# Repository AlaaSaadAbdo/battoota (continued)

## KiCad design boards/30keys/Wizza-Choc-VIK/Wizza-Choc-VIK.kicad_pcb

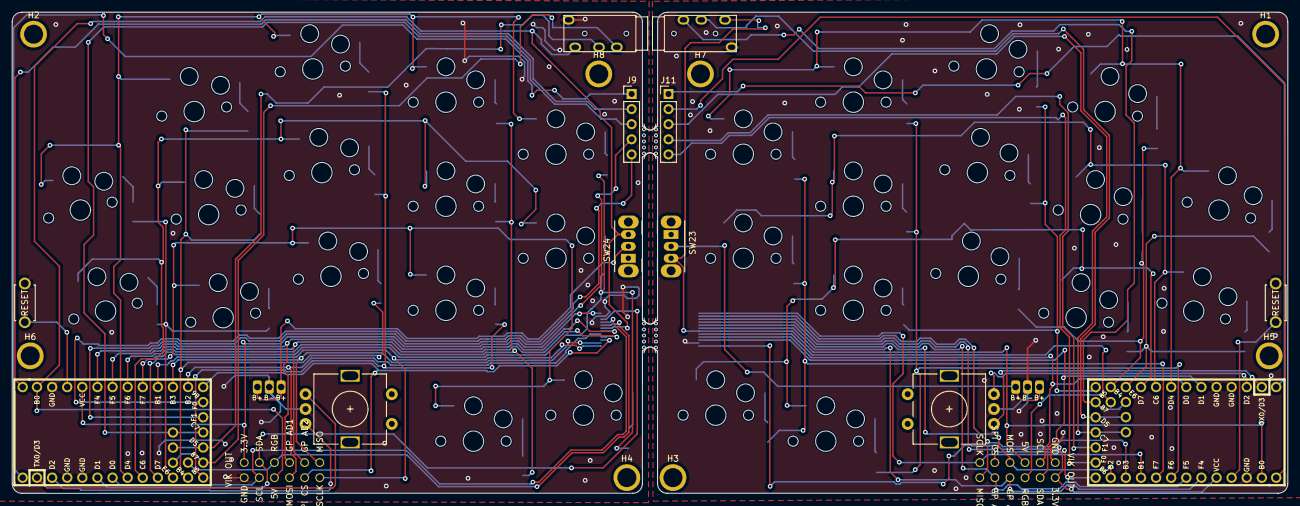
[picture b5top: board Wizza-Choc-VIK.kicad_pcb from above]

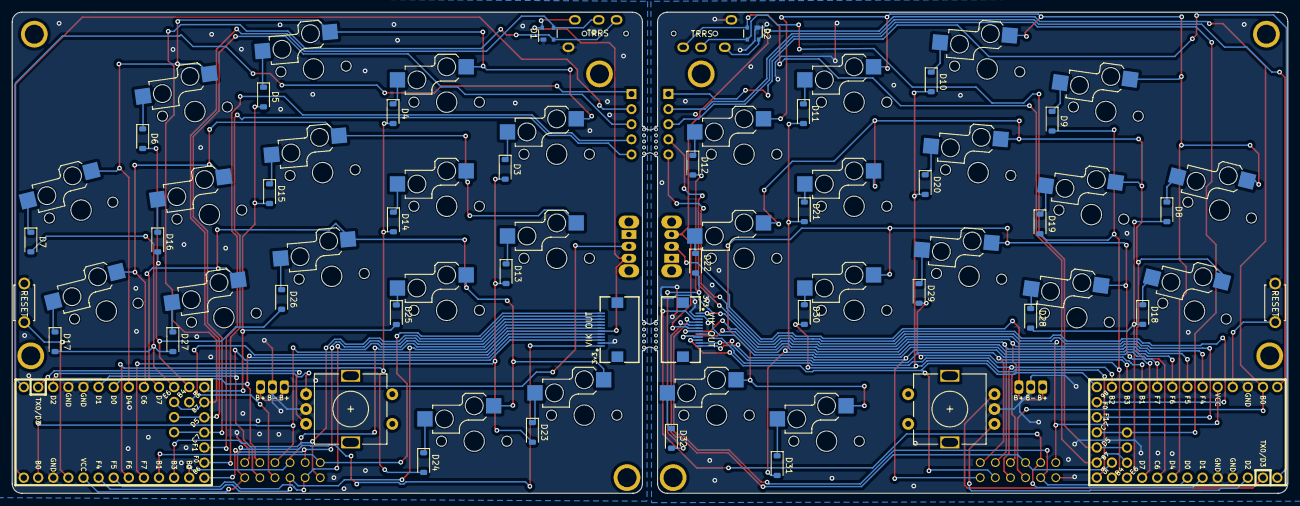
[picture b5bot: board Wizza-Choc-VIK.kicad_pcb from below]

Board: 2 copper layers, 214.5 x 80.9 mm, 90 parts (34 on the bottom side), 92 nets.

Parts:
D1, D2: PRTR5V0U2X; SOT-143
D3, D4, D5, D6, D7, D8, D9, D10, D11, D12, D13, D14, D15, D16, D17, D18, D19, D20, D21, D22, D23, D24, D25, D26, D27, D28, D29, D30, D31, D32: 1N4148; D_SOD-123
H1, H2, H3, H4, H5, H6, H7, H8: MountingHole; MountingHole_M3
J1, J2: AudioJack4dpb; TRRS-PJ-320A
J3, J4: Conn_01x03_Socket; 3JST_BAT
J5, J6: vik-keyboard-connector-horizontal
J7, J8: vik-keyboard-throughole
J9, J11: Conn_01x05; PinHeader_1x05_P2.54mm_Vertical
SW1, SW2, SW3, SW4, SW5, SW6, SW7, SW8, SW9, SW10, SW13, SW14, SW15, SW16, SW17, SW18, SW19, SW20, SW21, SW22, SW25, SW26, SW27, SW28, SW29, SW30, SW31, SW32, SW33, SW34: SW_Push; choc_hotswap
SW11, SW12: SW_Push; ResetSW
SW23, SW24: SW_SPDT; SW_CuK_OS102011MA1QN1_SPDT_Angled
SW35, SW36: Rotary_Encoder_Switch; RotaryEncoder_Alps_EC11E-Switch_Vertical_H20mm-keebio_modif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
U3, U4: Helios; Helios-Nano
mouse-bite-2mm-slot, mouse-bite-2mm-slot#2: VAL**; mouse-bite-5mm-slot-with-space-for-track

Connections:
BAT_L: J3.1, J3.3, SW24.2 (B)
BAT_R: J4.1, J4.3, SW23.2 (B)
EncL_L: SW35.B, U4.2 (RX1/PD2)
EncL_R: SW36.B, U3.2 (RX1/PD2)
EncR_L: SW35.A, U4.1 (TX0/PD3)
EncR_R: SW36.A, U3.1 (TX0/PD3)
GND_L: D2.1 (GND), J2.C, J3.2, J5.2 (GND), J7.2 (GND), SW12.2, SW35.C, U4.3 (GND), U4.4 (GND), U4.23 (GND)
GND_R: D1.1 (GND), J1.C, J4.2, J6.2 (GND), J8.2 (GND), SW11.2, SW36.C, U3.3 (GND), U3.4 (GND), U3.23 (GND)
GPIO10_L: J9.1, U4.31 (GPIO10)
GPIO10_R: J11.1, U3.31 (GPIO10)
GPIO11_L: J9.2, U4.32 (GPIO11)
GPIO11_R: J11.2, U3.32 (GPIO11)
GPIO14_L: J9.3, U4.27 (C7)
GPIO14_R: J11.3, U3.27 (C7)
GPIO15_L: J9.4, U4.28 (F1)
GPIO15_R: J11.4, U3.28 (F1)
GPIO16_L: J9.5, U4.29 (F0)
GPIO16_R: J11.5, U3.29 (F0)
LED_5V_L: J5.5 (RGB_LED_OUT), J7.5 (RGB_LED_OUT), U4.30 (RGB)
LED_5V_R: J6.5 (RGB_LED_OUT), J8.5 (RGB_LED_OUT), U3.30 (RGB)
MISO_L: J5.11 (MISO), J7.11 (MISO), U4.15 (14/PB3)
MISO_R: J6.11 (MISO), J8.11 (MISO), U3.15 (14/PB3)
MOSI_L: J5.8 (MOSI), J7.8 (MOSI), U4.14 (16/PB2)
MOSI_R: J6.8 (MOSI), J8.8 (MOSI), U3.14 (16/PB2)
NCS_L: J5.10 (SPI_CS), J7.10 (SPI_CS), U4.13 (10/PB6)
NCS_R: J6.10 (SPI_CS), J8.10 (SPI_CS), U3.13 (10/PB6)
unnamed: D3.1 (K), SW1.2
unnamed: D4.1 (K), SW2.2
unnamed: D5.1 (K), SW3.2
unnamed: D6.1 (K), SW4.2
unnamed: D7.1 (K), SW5.2
unnamed: D8.1 (K), SW6.2
unnamed: D9.1 (K), SW7.2
unnamed: D10.1 (K), SW8.2
unnamed: D11.1 (K), SW9.2
unnamed: D12.1 (K), SW10.2
unnamed: D13.1 (K), SW13.2
unnamed: D14.1 (K), SW14.2
unnamed: D15.1 (K), SW15.2
unnamed: D16.1 (K), SW16.2
unnamed: D17.1 (K), SW17.2
unnamed: D18.1 (K), SW18.2
unnamed: D19.1 (K), SW19.2
unnamed: D20.1 (K), SW20.2
unnamed: D21.1 (K), SW21.2
unnamed: D22.1 (K), SW22.2
unnamed: D23.1 (K), SW25.2
unnamed: D24.1 (K), SW26.2
unnamed: D25.1 (K), SW27.2
unnamed: D26.1 (K), SW28.2
unnamed: D27.1 (K), SW29.2
unnamed: D28.1 (K), SW30.2
unnamed: D29.1 (K), SW31.2
unnamed: D30.1 (K), SW32.2
unnamed: D31.1 (K), SW33.2
unnamed: D32.1 (K), SW34.2
RAW_L: D2.4 (VCC), J2.D, J5.6 (5V), J7.6 (5V), SW24.3 (C), U4.24 (B0)
RAW_R: D1.4 (VCC), J1.D, J6.6 (5V), J8.6 (5V), SW23.3 (C), U3.24 (B0)
RESET_L: SW12.1, U4.22 (RST)
RESET_R: SW11.1, U3.22 (RST)
RX_L: D2.3 (I/O2), J2.A, U4.26 (D5)
RX_R: D1.3 (I/O2), J1.A, U3.26 (D5)
SCLK_L: J5.12 (SCLK), J7.12 (SCLK), U4.16 (15/PB1)
SCLK_R: J6.12 (SCLK), J8.12 (SCLK), U3.16 (15/PB1)
SCL_L: J5.4 (SCL), J7.4 (SCL), U4.6 (3/PD0)
SCL_R: J6.4 (SCL), J8.4 (SCL), U3.6 (3/PD0)
SDA_L: J5.3 (SDA), J7.3 (SDA), U4.5 (2/PD1)
SDA_R: J6.3 (SDA), J8.3 (SDA), U3.5 (2/PD1)
TX_L: D2.2 (I/O1), J2.B, U4.25 (B7)
TX_R: D1.2 (I/O1), J1.B, U3.25 (B7)
VCC_L: J5.1 (3V3), J7.1 (3V3), U4.21 (VCC)
VCC_R: J6.1 (3V3), J8.1 (3V3), U3.21 (VCC)
VIK_AD1_L: J5.7 (GPIO_AD1), J7.7 (GPIO_AD1), U4.20 (A3/PF4)
VIK_AD1_R: J6.7 (GPIO_AD1), J8.7 (GPIO_AD1), U3.20 (A3/PF4)
VIK_AD2_L: J5.9 (GPIO_AD2), J7.9 (GPIO_AD2), U4.19 (A2/PF5)
VIK_AD2_R: J6.9 (GPIO_AD2), J8.9 (GPIO_AD2), U3.19 (A2/PF5)
col0_L: D8.2 (A), D18.2 (A), D28.2 (A), U4.10 (7/PE6)
col0_R: D7.2 (A), D17.2 (A), D27.2 (A), U3.10 (7/PE6)
col1_L: D9.2 (A), D19.2 (A), D29.2 (A), U4.11 (8/PB4)
col1_R: D6.2 (A), D16.2 (A), D26.2 (A), U3.11 (8/PB4)
col2_L: D10.2 (A), D20.2 (A), D30.2 (A), U4.12 (9/PB5)
col2_R: D5.2 (A), D15.2 (A), D25.2 (A), U3.12 (9/PB5)
col3_L: D11.2 (A), D21.2 (A), D31.2 (A), U4.18 (A1/PF6)
col3_R: D4.2 (A), D14.2 (A), D24.2 (A), U3.18 (A1/PF6)
col4_L: D12.2 (A), D22.2 (A), D32.2 (A), U4.17 (A0/PF7)
col4_R: D3.2 (A), D13.2 (A), D23.2 (A), U3.17 (A0/PF7)
row_0_L: SW6.1, SW7.1, SW8.1, SW9.1, SW10.1, U4.7 (4/PD4)
row_0_R: SW1.1, SW2.1, SW3.1, SW4.1, SW5.1, U3.7 (4/PD4)
row_1_L: SW18.1, SW19.1, SW20.1, SW21.1, SW22.1, U4.8 (5/PC6)
row_1_R: SW13.1, SW14.1, SW15.1, SW16.1, SW17.1, U3.8 (5/PC6)
row_2_L: SW30.1, SW31.1, SW32.1, SW33.1, SW34.1, U4.9 (6/PD7)
row_2_R: SW25.1, SW26.1, SW27.1, SW28.1, SW29.1, U3.9 (6/PD7)

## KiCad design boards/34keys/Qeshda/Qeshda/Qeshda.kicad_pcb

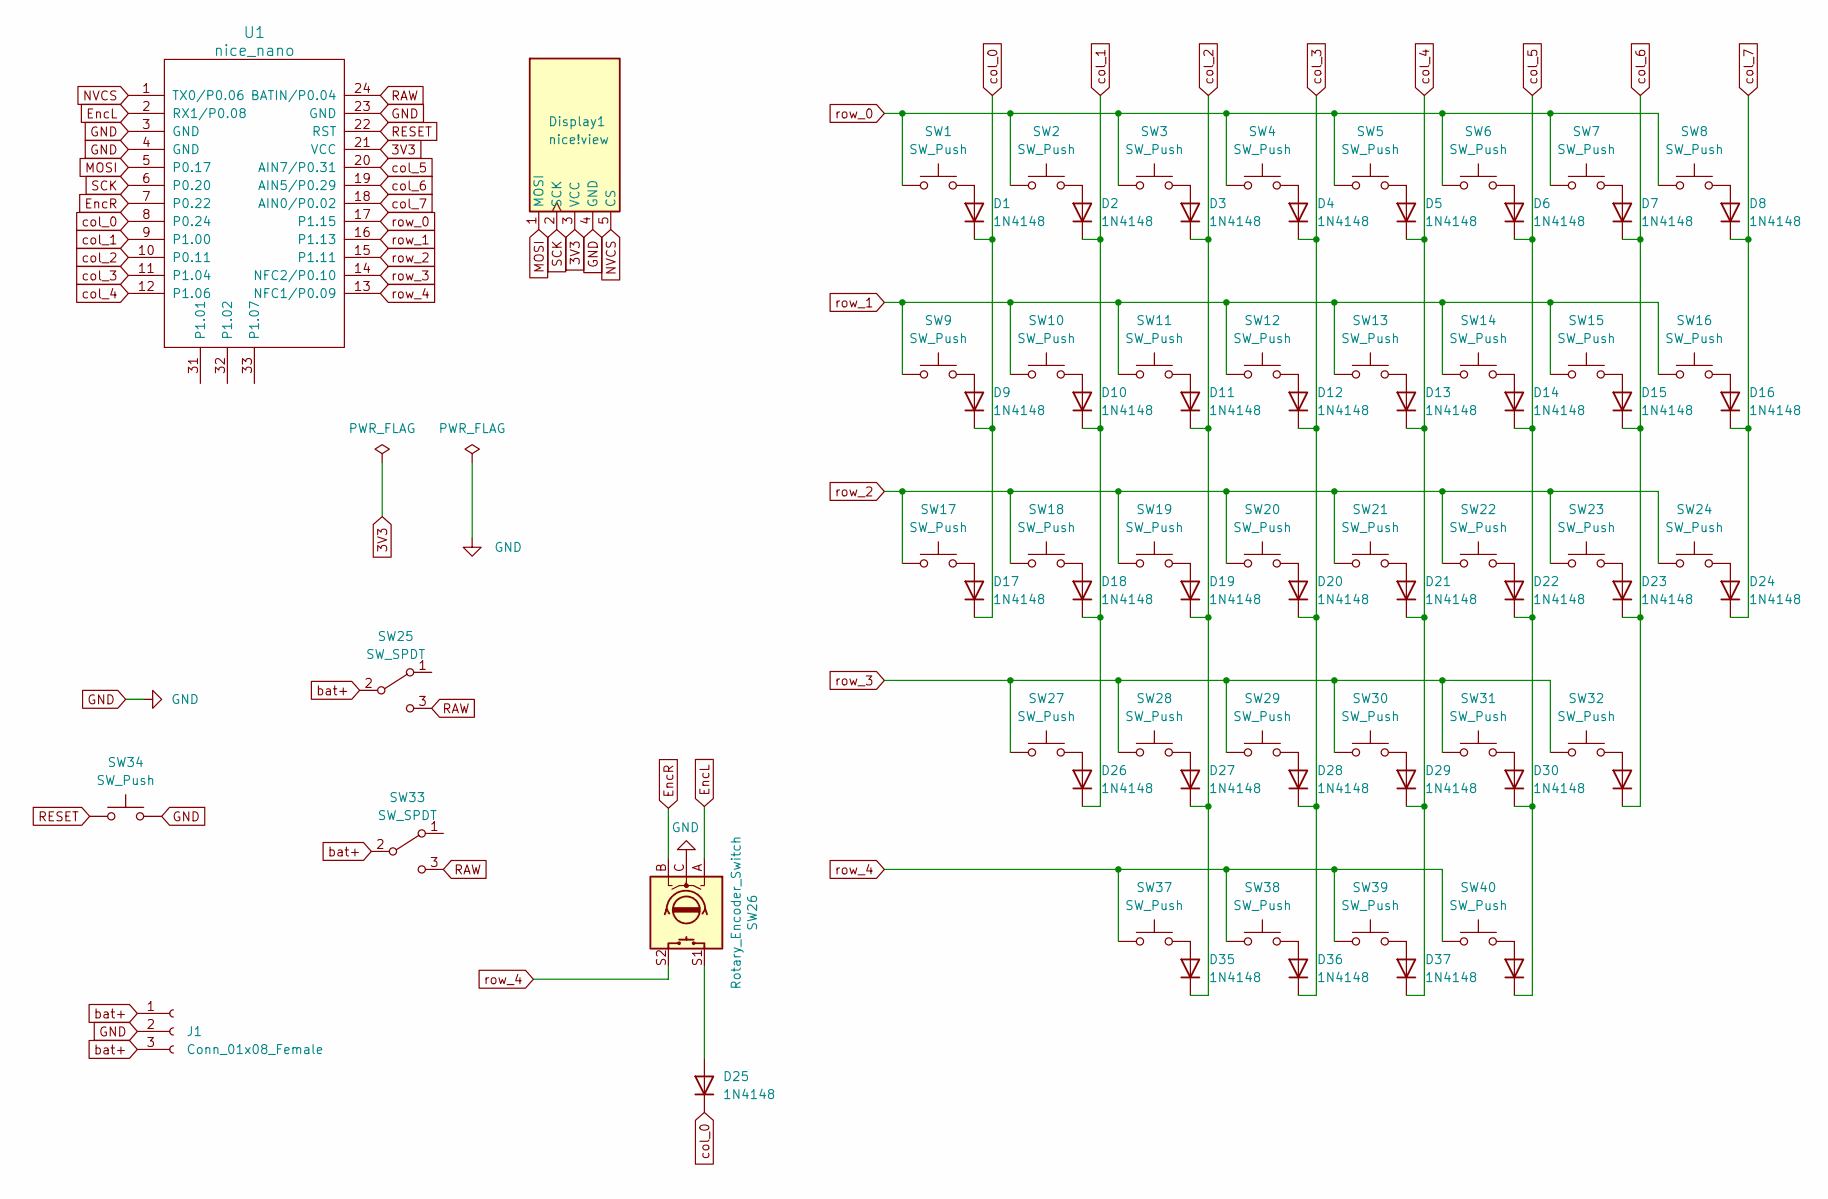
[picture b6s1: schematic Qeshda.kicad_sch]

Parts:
D1, D2, D3, D4, D5, D6, D7, D8, D9, D10, D11, D12, D13, D14, D15, D16, D17, D18, D19, D20, D21, D22, D23, D24, D25, D26, D27, D28, D29, D30, D31, D35, D36, D37, D38: 1N4148; D_SOD-123; LCSC C909967
Display1: nice!view; nice_view
J1: Conn_01x08_Female; 3JST_BAT
SW1, SW2, SW3, SW4, SW5, SW6, SW7, SW8, SW9, SW10, SW11, SW12, SW13, SW14, SW15, SW16, SW17, SW18, SW19, SW20, SW21, SW22, SW23, SW24, SW27, SW28, SW29, SW30, SW31, SW32, SW37, SW38, SW39, SW40: SW_Push; choc_hotswap
SW25, SW33: SW_SPDT; SW_SPDT_PCM12
SW26: Rotary_Encoder_Switch; RotaryEncoder_Alps_EC11E-Switch_Vertical_H20mm-keebio_modif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
SW34: SW_Push; ResetSW
U1: nice_nano

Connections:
3V3: Display1.3 (VCC), U1.21 (VCC)
EncL: SW26.A, U1.2 (RX1/P0.08)
EncR: SW26.B, U1.7 (P0.22)
GND: Display1.4 (GND), J1.2, SW26.C, SW34.2, U1.3 (GND), U1.4 (GND), U1.23 (GND)
MOSI: Display1.1 (MOSI), U1.5 (P0.17)
NVCS: Display1.5 (CS), U1.1 (TX0/P0.06)
unnamed: D1.2 (A), SW1.2
unnamed: D2.2 (A), SW2.2
unnamed: D3.2 (A), SW3.2
unnamed: D4.2 (A), SW4.2
unnamed: D5.2 (A), SW5.2
unnamed: D6.2 (A), SW6.2
unnamed: D7.2 (A), SW7.2
unnamed: D8.2 (A), SW8.2
unnamed: D9.2 (A), SW9.2
unnamed: D10.2 (A), SW10.2
unnamed: D11.2 (A), SW11.2
unnamed: D12.2 (A), SW12.2
unnamed: D13.2 (A), SW13.2
unnamed: D14.2 (A), SW14.2
unnamed: D15.2 (A), SW15.2
unnamed: D16.2 (A), SW16.2
unnamed: D17.2 (A), SW17.2
unnamed: D18.2 (A), SW18.2
unnamed: D19.2 (A), SW19.2
unnamed: D20.2 (A), SW20.2
unnamed: D21.2 (A), SW21.2
unnamed: D22.2 (A), SW22.2
unnamed: D23.2 (A), SW23.2
unnamed: D24.2 (A), SW24.2
unnamed: D25.2 (A), SW26.S1
unnamed: D26.2 (A), SW27.2
unnamed: D27.2 (A), SW28.2
unnamed: D28.2 (A), SW29.2
unnamed: D29.2 (A), SW30.2
unnamed: D30.2 (A), SW31.2
unnamed: D31.2 (A), SW32.2
unnamed: D35.2 (A), SW37.2
unnamed: D36.2 (A), SW38.2
unnamed: D37.2 (A), SW39.2
unnamed: D38.2 (A), SW40.2
RAW: SW25.3 (C), SW33.3 (C), U1.24 (BATIN/P0.04)
RESET: SW34.1, U1.22 (RST)
SCK: Display1.2 (SCK), U1.6 (P0.20)
bat+: J1.1, J1.3, SW25.2 (B), SW33.2 (B)
col_0: D1.1 (K), D9.1 (K), D17.1 (K), D25.1 (K), U1.8 (P0.24)
col_1: D2.1 (K), D10.1 (K), D18.1 (K), D26.1 (K), U1.9 (P1.00)
col_2: D3.1 (K), D11.1 (K), D19.1 (K), D27.1 (K), D35.1 (K), U1.10 (P0.11)
col_3: D4.1 (K), D12.1 (K), D20.1 (K), D28.1 (K), D36.1 (K), U1.11 (P1.04)
col_4: D5.1 (K), D13.1 (K), D21.1 (K), D29.1 (K), D37.1 (K), U1.12 (P1.06)
col_5: D6.1 (K), D14.1 (K), D22.1 (K), D30.1 (K), D38.1 (K), U1.20 (AIN7/P0.31)
col_6: D7.1 (K), D15.1 (K), D23.1 (K), D31.1 (K), U1.19 (AIN5/P0.29)
col_7: D8.1 (K), D16.1 (K), D24.1 (K), U1.18 (AIN0/P0.02)
row_0: SW1.1, SW2.1, SW3.1, SW4.1, SW5.1, SW6.1, SW7.1, SW8.1, U1.17 (P1.15)
row_1: SW9.1, SW10.1, SW11.1, SW12.1, SW13.1, SW14.1, SW15.1, SW16.1, U1.16 (P1.13)
row_2: SW17.1, SW18.1, SW19.1, SW20.1, SW21.1, SW22.1, SW23.1, SW24.1, U1.15 (P1.11)
row_3: SW27.1, SW28.1, SW29.1, SW30.1, SW31.1, SW32.1, U1.14 (NFC2/P0.10)
row_4: SW26.S2, SW37.1, SW38.1, SW39.1, SW40.1, U1.13 (NFC1/P0.09)

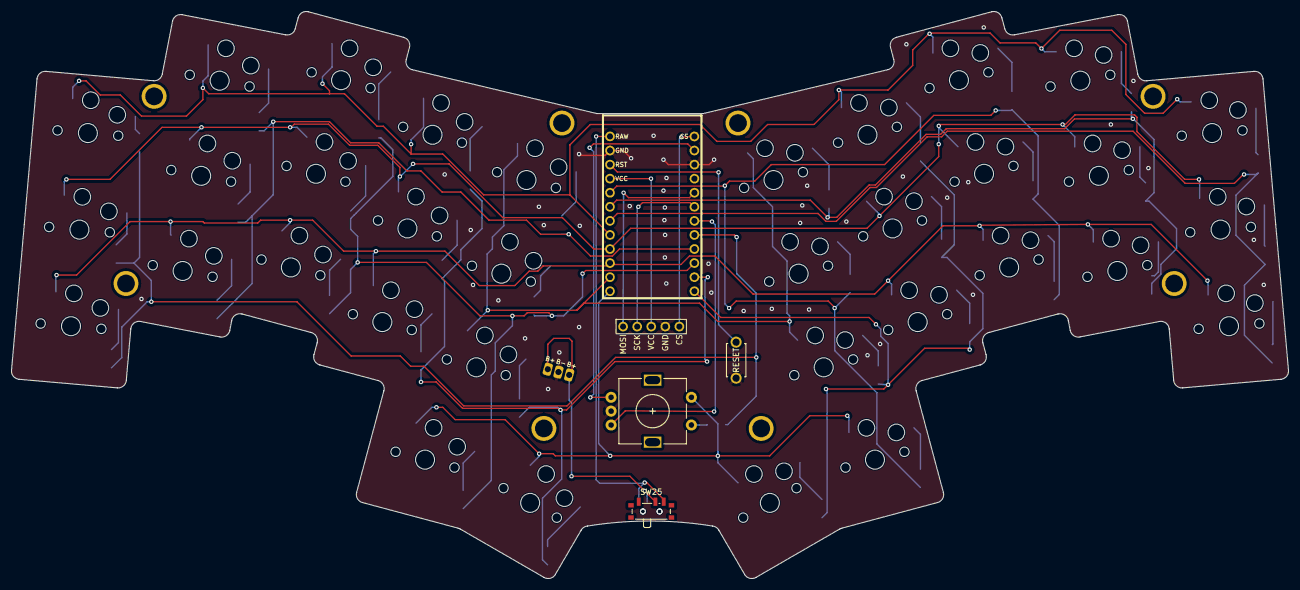
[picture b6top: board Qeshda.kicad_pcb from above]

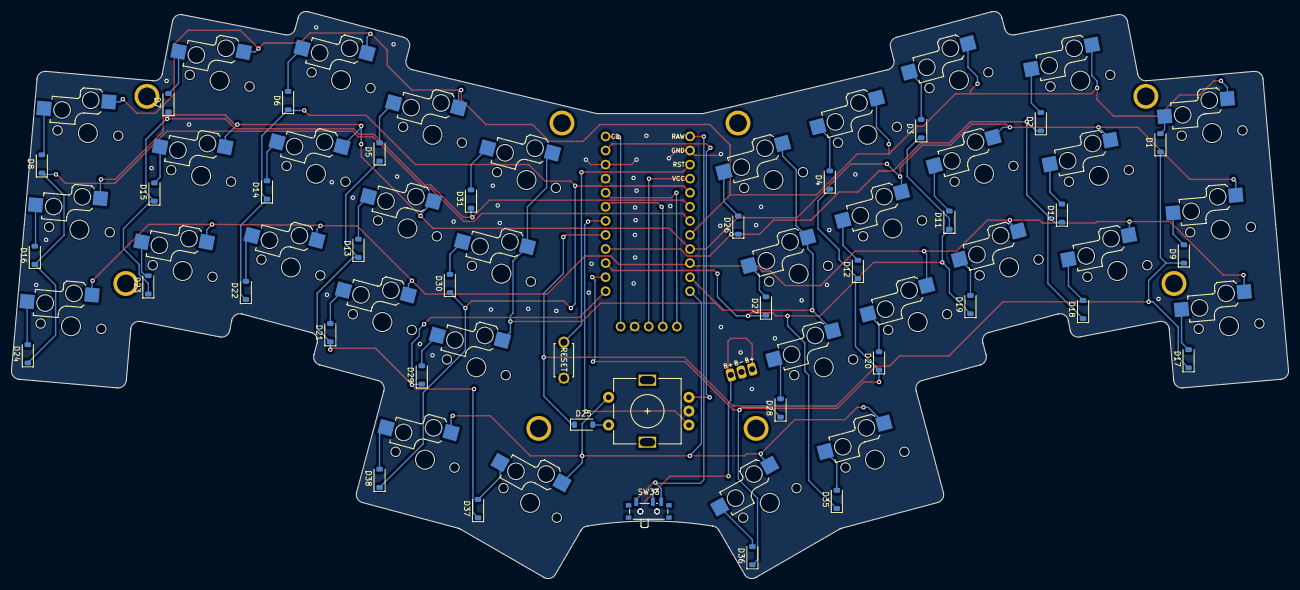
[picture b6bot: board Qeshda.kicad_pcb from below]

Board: 2 copper layers, 230.5 x 102.4 mm, 76 parts (37 on the bottom side), 58 nets.

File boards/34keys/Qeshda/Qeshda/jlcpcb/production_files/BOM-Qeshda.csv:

Comment,Designator,Footprint,LCSC
1N4148,"D1,D10,D11,D12,D13,D14,D15,D16,D17,D18,D19,D2,D20,D21,D22,D23,D24,D25,D26,D27,D28,D29,D3,D30,D31,D35,D36,D37,D38,D4,D5,D6,D7,D8,D9",D_SOD-123,C909967
Conn_01x08_Female,J1,3JST_BAT,
nice_nano,U1,nice_nano,
SW_Push,SW21,choc_hotswap,
SW_Push,SW30,choc_hotswap,
SW_Push,SW22,choc_hotswap,
Rotary_Encoder_Switch,SW26,RotaryEncoder_Alps_EC11E-Switch_Vertical_H20mm-keebio_modified,
SW_Push,SW34,ResetSW,
SW_Push,SW40,choc_hotswap,
SW_Push,SW39,choc_hotswap,
SW_Push,SW38,choc_hotswap,
SW_Push,SW37,choc_hotswap,
SW_Push,SW32,choc_hotswap,
SW_Push,SW31,choc_hotswap,
SW_Push,SW29,choc_hotswap,
SW_Push,SW28,choc_hotswap,
SW_Push,SW27,choc_hotswap,
SW_SPDT,SW25,SW_SPDT_PCM12,
SW_Push,SW24,choc_hotswap,
SW_Push,SW23,choc_hotswap,
SW_Push,SW20,choc_hotswap,
SW_Push,SW19,choc_hotswap,
SW_Push,SW18,choc_hotswap,
SW_Push,SW17,choc_hotswap,
SW_Push,SW16,choc_hotswap,
SW_Push,SW15,choc_hotswap,
SW_Push,SW14,choc_hotswap,
SW_Push,SW13,choc_hotswap,
SW_Push,SW12,choc_hotswap,
SW_Push,SW11,choc_hotswap,
SW_Push,SW10,choc_hotswap,
SW_Push,SW9,choc_hotswap,
SW_Push,SW8,choc_hotswap,
SW_Push,SW7,choc_hotswap,
SW_Push,SW6,choc_hotswap,
SW_Push,SW5,choc_hotswap,
SW_Push,SW4,choc_hotswap,
SW_Push,SW3,choc_hotswap,
SW_Push,SW2,choc_hotswap,
SW_Push,SW1,choc_hotswap,
nice!view,Display1,nice_view,
SW_SPDT,SW33,SW_SPDT_PCM12,

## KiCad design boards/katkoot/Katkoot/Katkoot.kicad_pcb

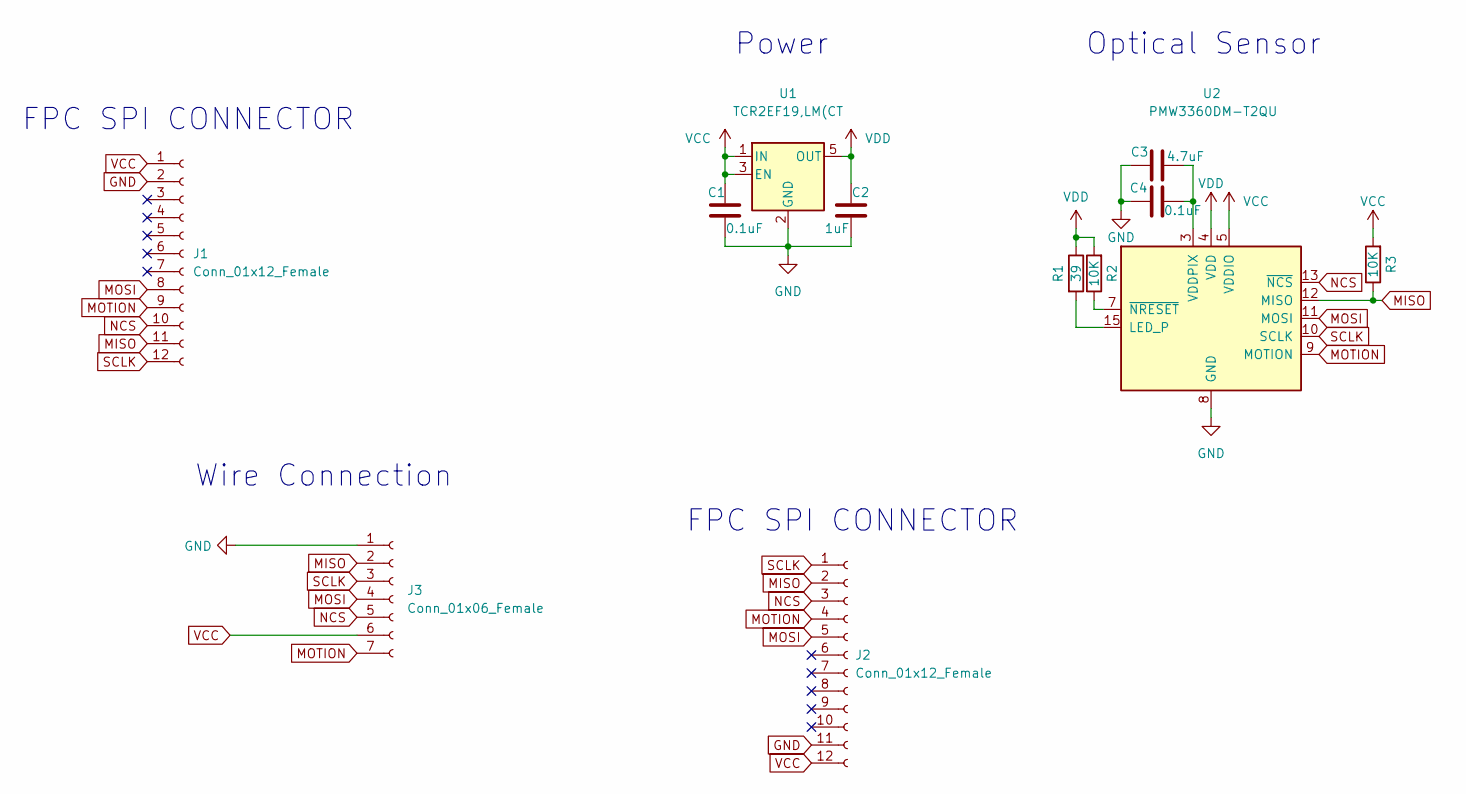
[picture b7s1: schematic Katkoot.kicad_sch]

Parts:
C1, C4: 0.1uF; C_0805_2012Metric; LCSC C77456
C2: 1uF; C_0805_2012Metric; LCSC C366879
C3: 4.7uF; C_0805_2012Metric; LCSC C303940
J1, J2: Conn_01x12_Female; FPC-SMD_FPC05012-09200-.5mm-rev; LCSC C479750
J3: Conn_01x06_Female
R1: 39; R_0805_2012Metric; LCSC C514993
R2, R3: 10K; R_0805_2012Metric; LCSC C406725
U1: TCR2EF19,LM(CT; SOT-23-5; LCSC C146366
U2: PMW3360DM-T2QU

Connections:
GND: C1.2, C2.2, C3.2, C4.1, J1.2, J2.11, J3.1, U1.2 (GND), U2.8 (GND)
MISO: J1.11, J2.2, J3.2, R3.1, U2.12 (MISO)
MOSI: J1.8, J2.5, J3.4, U2.11 (MOSI)
MOTION: J1.9, J2.4, J3.7, U2.9 (MOTION)
NCS: J1.10, J2.3, J3.5, U2.13 (~NCS)
unnamed: C3.1, C4.2, U2.3 (VDDPIX)
unnamed: R1.2, U2.15 (LED_P)
unnamed: R2.1, U2.7 (~NRESET)
SCLK: J1.12, J2.1, J3.3, U2.10 (SCLK)
VCC: C1.1, J1.1, J2.12, J3.6, R3.2, U1.1 (IN), U1.3 (EN), U2.5 (VDDIO)
VDD: C2.1, R1.1, R2.2, U1.5 (OUT), U2.4 (VDD)

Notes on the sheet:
Power
FPC SPI CONNECTOR
Optical Sensor
Wire Connection

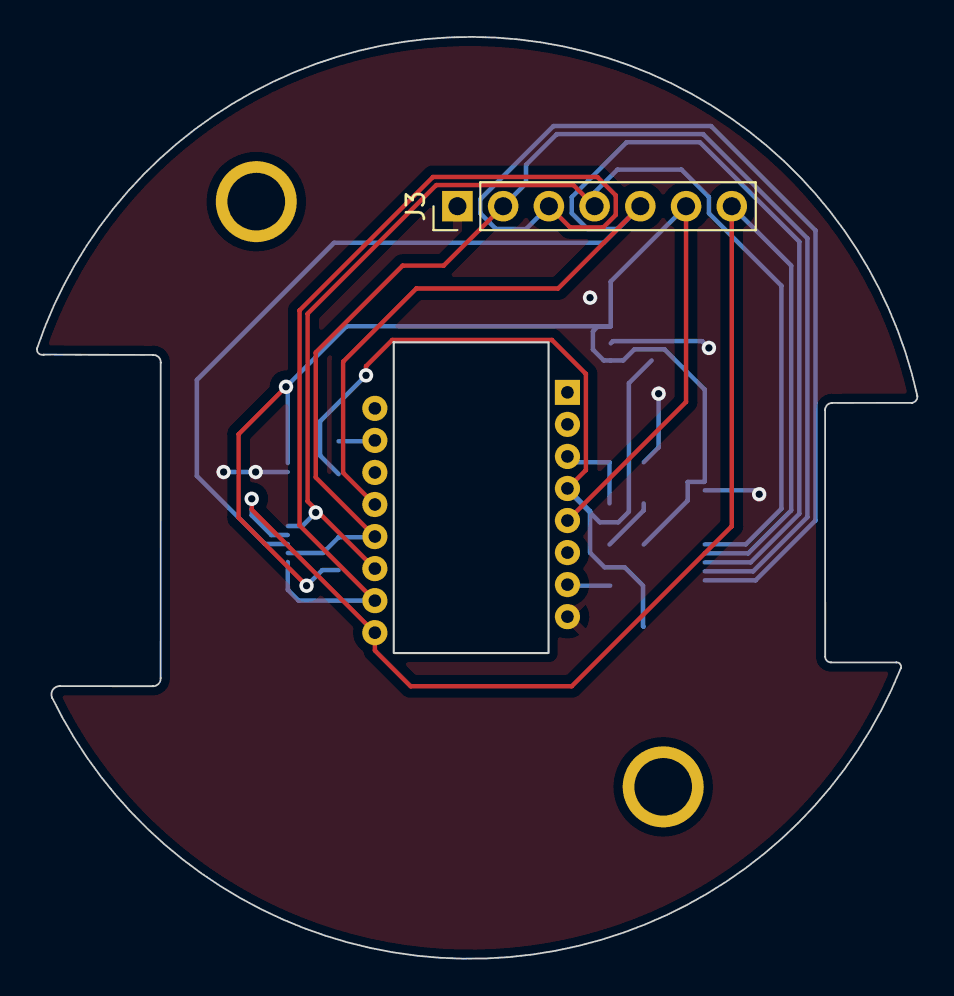
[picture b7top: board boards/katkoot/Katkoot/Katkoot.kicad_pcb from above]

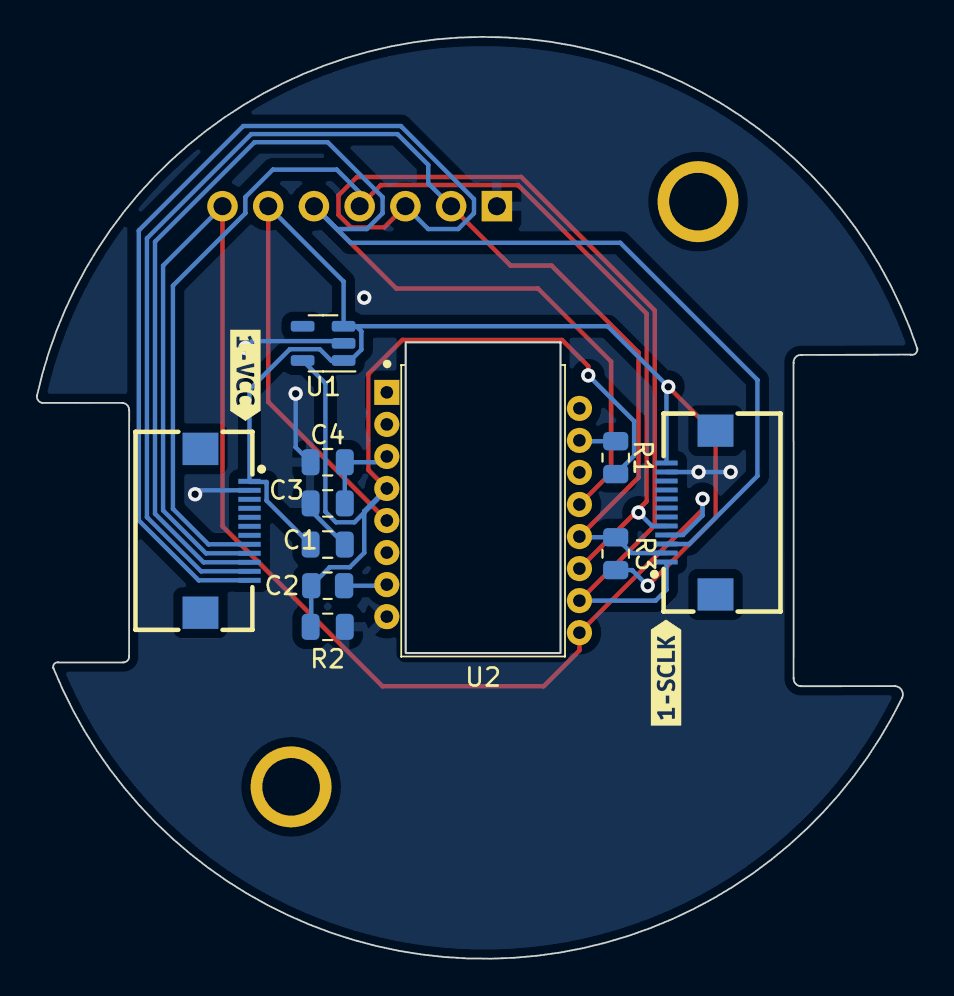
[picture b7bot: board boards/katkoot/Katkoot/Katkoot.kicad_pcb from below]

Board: 2 copper layers, 48.9 x 51.2 mm, 14 parts (13 on the bottom side), 11 nets.

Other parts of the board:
kibuzzard-63793EB1: G***; kibuzzard-63793EB1
kibuzzard-63793EC8: G***; kibuzzard-63793EC8

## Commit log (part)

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2022-04-27 image path
2022-04-28 mini
2022-04-28 mini image
2022-04-28 batta is here
2022-04-28 mini dir rename
2022-04-28 clean router in batta main
2022-04-28 image with cleaner routes
2022-04-29 mini routing modification
2022-04-29 updated gerber
2022-05-01 Add reversable mini
2022-05-01 bata mini
2022-05-01 remove b- and b+
2022-05-01 30 key image link
2022-05-01 rename the via
2022-05-01 battoota
2022-05-01 remove empty dir
2022-05-02 missimg kb logo in battoota
2022-05-08 battoota curvy
2022-05-11 fix gnd issue in 30 keys
2022-05-12 battoota lower index
2022-05-13 remove curvy and make inner index closer
2022-05-13 update battoota design
2022-05-13 remove curvy and add changed image
2022-05-13 pcb shape change
2022-05-15 batoota tent
2022-05-15 Experiments with inverted index
2022-05-16 shorter thumb
2022-05-17 keeb picture
2022-05-17 batta tenting improve shape
2022-05-20 rectangle battoota
2022-05-21 more uniform rectangle for battoota
2022-05-23 Case files
2022-05-23 battoota recctangle uniform
2022-05-24 move jst location on lower index
2022-05-24 batta
2022-05-24 f3d files
2022-05-25 batta rectangle
2022-05-27 ney keebs
2022-05-27 ergo gen file for batta
2022-05-27 add batta and battoota from ergogen
2022-05-27 add pretty mcu version
2022-05-28 add on/off switch to ergogen version
2022-05-28 fix on/off position
2022-05-28 addo missing slider dimentions
2022-05-28 use default footprints
2022-05-29 clean up experiments
2022-05-29 images
2022-05-29 doc again
2022-06-08 basbousa intro
2022-06-13 konafa
2022-06-13 fix stagger on index
2022-06-13 konafa cleanup
2022-06-13 battoota clean up
2022-06-13 basbousa
2022-06-14 min choc battoota
2022-06-14 konafa pictures
2022-06-14 min choc versions
2022-06-15 min versions routing
2022-06-15 cleanup ergogen files
2022-06-17 move lower index to experiments
2022-06-17 clean up all the boards
2022-06-21 move mcu on battoota up
2022-07-01 update boards
2022-07-06 min changes
2022-07-08 new size battoota
2022-07-09 basbousa gerber
2022-07-21 wizza
2022-07-21 move cases of wizza
2022-07-22 new cases for wizza
2022-07-25 battoota thumb to original place
2022-07-25 added battoota with 3 thumbs
2022-07-26 wizza choc v2
2022-07-27 basbousa new case with holes and chocV2 change
2022-07-30 reorganize the directories
2022-07-30 case dir in wizza and battoota
2022-07-31 new cases for konafa and battoota
2022-08-10 Add github workflow
2022-08-10 Rename konafa directory
2022-08-10 Update workflow paths
2022-08-10 Update gallery (automated)
2022-08-10 Use kikit nightly
2022-08-10 Wizza yml
2022-08-10 battoota edge cuts to 0
2022-08-10 restore width
2022-08-11 fix mcu on wizza chocV2
2022-08-11 use bcbdwraw with fix
2022-08-11 change areas for better pictures
2022-08-11 auto gallery
2022-08-11 3 thumb preview
2022-08-11 battota preview
2022-08-14 fix: ergogen wizza
2022-08-18 wizza mx
2022-08-18 same nets for all boards
2022-08-18 skip bottom in all ergogen
2022-08-18 Add License
2022-08-18 Create license
2022-08-21 asfoora v0.1
2022-08-21 Asfoora
2022-08-21 render Asfoora
2022-08-21 add jst connector to asfoor
2022-08-22 cases for chocV2 board
2022-08-23 asfoora changes
2022-08-23 asfoora battery hole
2022-08-23 M3 mounting holes
2022-08-23 Adjust spacing on Asfoora
2022-08-23 match mounting holes
2022-08-27 update asfoora and wizza mx
2022-09-03 asfoora rotate jst footprint
2022-09-03 Wizza-chocV1-MX_Spacing
2022-09-03 case for Wizza-chocV1-MX_Spacing
2022-09-03 change mx footprint
2022-09-03 plot wizza mx
2022-09-04 re-arrange readme
2022-09-04 docs
2022-09-06 asfoora improvements
2022-09-07 new asfoora bom
2022-09-21 Active roster
2022-10-02 add logo to choc V2 board
2022-10-03 pictures dir
2022-10-17 Batreeq
2022-10-17 correct diode direction
2022-10-17 remove jlc plugin files
2022-10-18 batreeq step and svg
2022-10-20 version sent to fab
2022-11-04 fix batreeq bodge and mcu footprint
2022-11-04 Gerber of fixed MCU footprint
2022-11-05 render Batreeq PCB and picture
2022-11-05 Batreeq Case files
2022-11-05 Rename LICENSE to LICENSE.md
2022-11-05 add credits and references
2022-11-05 replace cirque rectangle hole with lines
2022-11-05 kibot initial commit
2022-11-05 fix kibot yaml
2022-11-05 fix uses
2022-11-05 yaml again
2022-11-05 add checkout back in
2022-11-05 forgot steps
2022-11-05 add runs-on
2022-11-05 update boards path
2022-11-05 ls dir
2022-11-05 fix names
2022-11-05 fix tipo in ls command
2022-11-05 ls specific dir
2022-11-05 fix wrong slash
2022-11-05 ls konafa
2022-11-06 rename konafa
2022-11-06 change kibot config
2022-11-06 blue kibot
2022-11-06 case for choc
2022-11-06 gallery dir
2022-11-06 publish, maybe?
2022-11-06 fix yaml
2022-11-06 single quotation mark?
2022-11-06 fix path to images
2022-11-06 correct dir name
2022-11-06 correct image path
2022-11-06 fix path again. Also, I hate YAML
2022-11-06 ls images
2022-11-06 change images to gallery
2022-11-06 render and upload dir
2022-11-06 try to upload dir
2022-11-06 reference new images!
2022-11-06 remove old workflow
2022-11-06 try removing artifact dir
2022-11-06 rename artifact
2022-11-06 rename to images
2022-11-06 start from scratch
2022-11-06 upload dir
2022-11-06 remove gallery
2022-11-06 fix paths to pcb_images
2022-11-19 fix workflow?
2022-11-19 copy to the right path
2022-11-19 workflow again
2022-11-19 workflow remove old images
2022-11-19 maybe now?
2022-11-19 now?
2022-11-19 katkoot
2022-11-19 Cirque mounts
2022-11-19 fix flow
2022-11-20 fixed gnd issue in katkoot
2022-11-20 katkoot resize zone
2022-11-20 built in BTU a bit higher
2022-11-23 change kibot to not run on all file changes
2022-12-08 batreeqV2 untested
2022-12-08 fix: batreeq versions in CI
2022-12-08 add batreeq v2 image
2022-12-08 doc: fix batreeq V2 path
2022-12-18 batreeqv2
2022-12-18 batreeq svg update
2022-12-27 update family picture
2022-12-27 modify the screen cover.
2022-12-28 batreeq top plate
2022-12-28 add scroll ring and trackball mount to batreeq v2 case file
2022-12-29 add a wider version of the bottom plate for JLC
2022-12-29 Add the correct bottom plate for JLC
2022-12-29 clean up case files for Batreeq
2022-12-29 align new bottom plate
2022-12-29 remove old trackball mount
2022-12-30 add screen cover back
2022-12-30 screen cover update
2022-12-30 improved top plate
2022-12-30 improved screen holes
2022-12-30 screen cover tighter tolerance
2022-12-30 3D printing tolerances
2022-12-30 higher PLA scroll ring
2022-12-30 foam dxf
2023-01-01 add scroll ring and mount version 2
2023-01-01 new scroll ring and trackball mount
2023-01-05 batreeq 36
2023-01-05 batreeq36 not routed yet
2023-01-07 Routed the Batreeq36
2023-01-07 Batreeq36
2023-01-08 Zazu
2023-01-08 fix bottom plate
2023-01-08 split case
2023-01-08 zazo gerbers
2023-01-08 remove old bom/pos
2023-01-08 change Zazu's reset switch
2023-01-09 add reset hole to Zazu's bottom plate
2023-01-16 add resistors to scroll ring circuit
2023-01-16 move zazo to 40keys dir
2023-01-16 zazu ci/cd
2023-01-16 zazu pcb image in read me
2023-01-19 zazu fix rgb chain
2023-01-19 fix zazu rgb chain and merge
2023-01-23 update screen hole offset
2023-01-23 middle part offset
2023-01-23 fix case
2023-01-23 5 way cap shorter hole
2023-01-23 top plate heat insert hole size change
2023-01-25 zazu picture
2023-01-25 Add kyek to credits
2023-01-25 fix: tighter M3 inserts
2023-01-27 rename trackball mount
2023-01-27 flat 5 way key cap
2023-01-27 Bottom 3 piece split
2023-01-29 Wizza case
2023-01-29 Zazu Foam with hole for PMW sensor
2023-01-29 regenerate zazu gerber
2023-02-06 zazu step file
2023-02-06 asfoora new case
2023-02-07 switch plate foam
2023-02-07 asfoora case
2023-02-22 Zazu case: looser tolerances
2023-02-27 zazu build guide dir
2023-02-27 wired split init
2023-03-08 wired split update
2023-03-21 wired wizza
2023-03-25 add wired wizza to auto-render
2023-03-25 update kibot version
2023-03-25 change kibot tag
2023-03-25 Add wired Wizza to readme PCB preview
2023-03-29 fix wired wizza LEDs
2023-04-14 PER56 footprint
2023-04-14 wired wizza Picture
2023-05-02 Block initial commit
2023-05-02 block more routing
2023-05-02 case for wired wizza
2023-05-02 block routed and jlc files
2023-05-03 block updated level shifter
2023-05-03 block case
2023-05-12 Barghoot
2023-05-13 add grinnie, weteor & aki to credits
2023-05-15 Pictures: BatreeqV2 Rectangle & Barghoot
2023-05-15 fix wired wizza link
2023-05-15 remove todo and specifications for pcbs as they don't apply anymore
2023-05-17 barghoot readme
2023-05-22 barghoot screen and encoder covers
2023-05-29 Bolbol board
2023-06-29 Qeshda PCB
2023-06-30 More space for encoder in Qeschda
2023-06-30 Qeshda update
2023-06-30 Qeshda symmetry in mounting holes
2023-06-30 Qeshda move JST connector to have more space
2023-06-30 Qeshda gerbers update
2023-06-30 Qeshda: JST connector angled
2023-08-09 xiao and vik wizzas
2023-08-16 misc
2023-08-16 generate DXF tutorial
2023-08-16 fix: Plot dxf image
2023-08-17 wizza mx vik
2023-08-22 wizza vik
2023-08-22 wizza vik choc
2023-09-06 add vik 18 pin ffc
2023-09-19 katkoot vik
2023-09-19 wizza on off
2023-09-29 wizza mx new gerbers
2023-09-29 remove BOM and CPL for wizza MX
2023-09-29 Wizza with better on off switch
2023-09-29 Gerber for wizza MX
2023-10-04 VIK Katkoot
2024-04-17 wireless asfoora and katkoot
2024-04-18 fix 5 way switch on wasfoora
2024-04-18 wider hole for the 5 way on wasfoora
2024-06-25 move katkoot keys 1 key to the left
2024-06-25 update katkoot case
2024-06-30 updated batreeqV2 bom and cpl files for JLCPCB
2024-07-01 add wizza choc tray case for _lambchopchop
2024-07-05 BatreeqV2 readme
2024-07-26 wireless batreeq
2024-07-27 fix wireless batreeq reset ground pin schematic
2024-07-27 add space for JST cable in wireless batreeq
2024-07-27 rename batreeq wireless to Ghazal
2024-07-27 Add Ghazal readme
2024-07-28 Ghazal footprints
2024-08-02 Add Chewie to credits
2024-10-08 Organize Ghazal case files
2024-10-08 Asfoora negative tilt and no 5 way switch top
2024-10-08 fix Ghazal readme
